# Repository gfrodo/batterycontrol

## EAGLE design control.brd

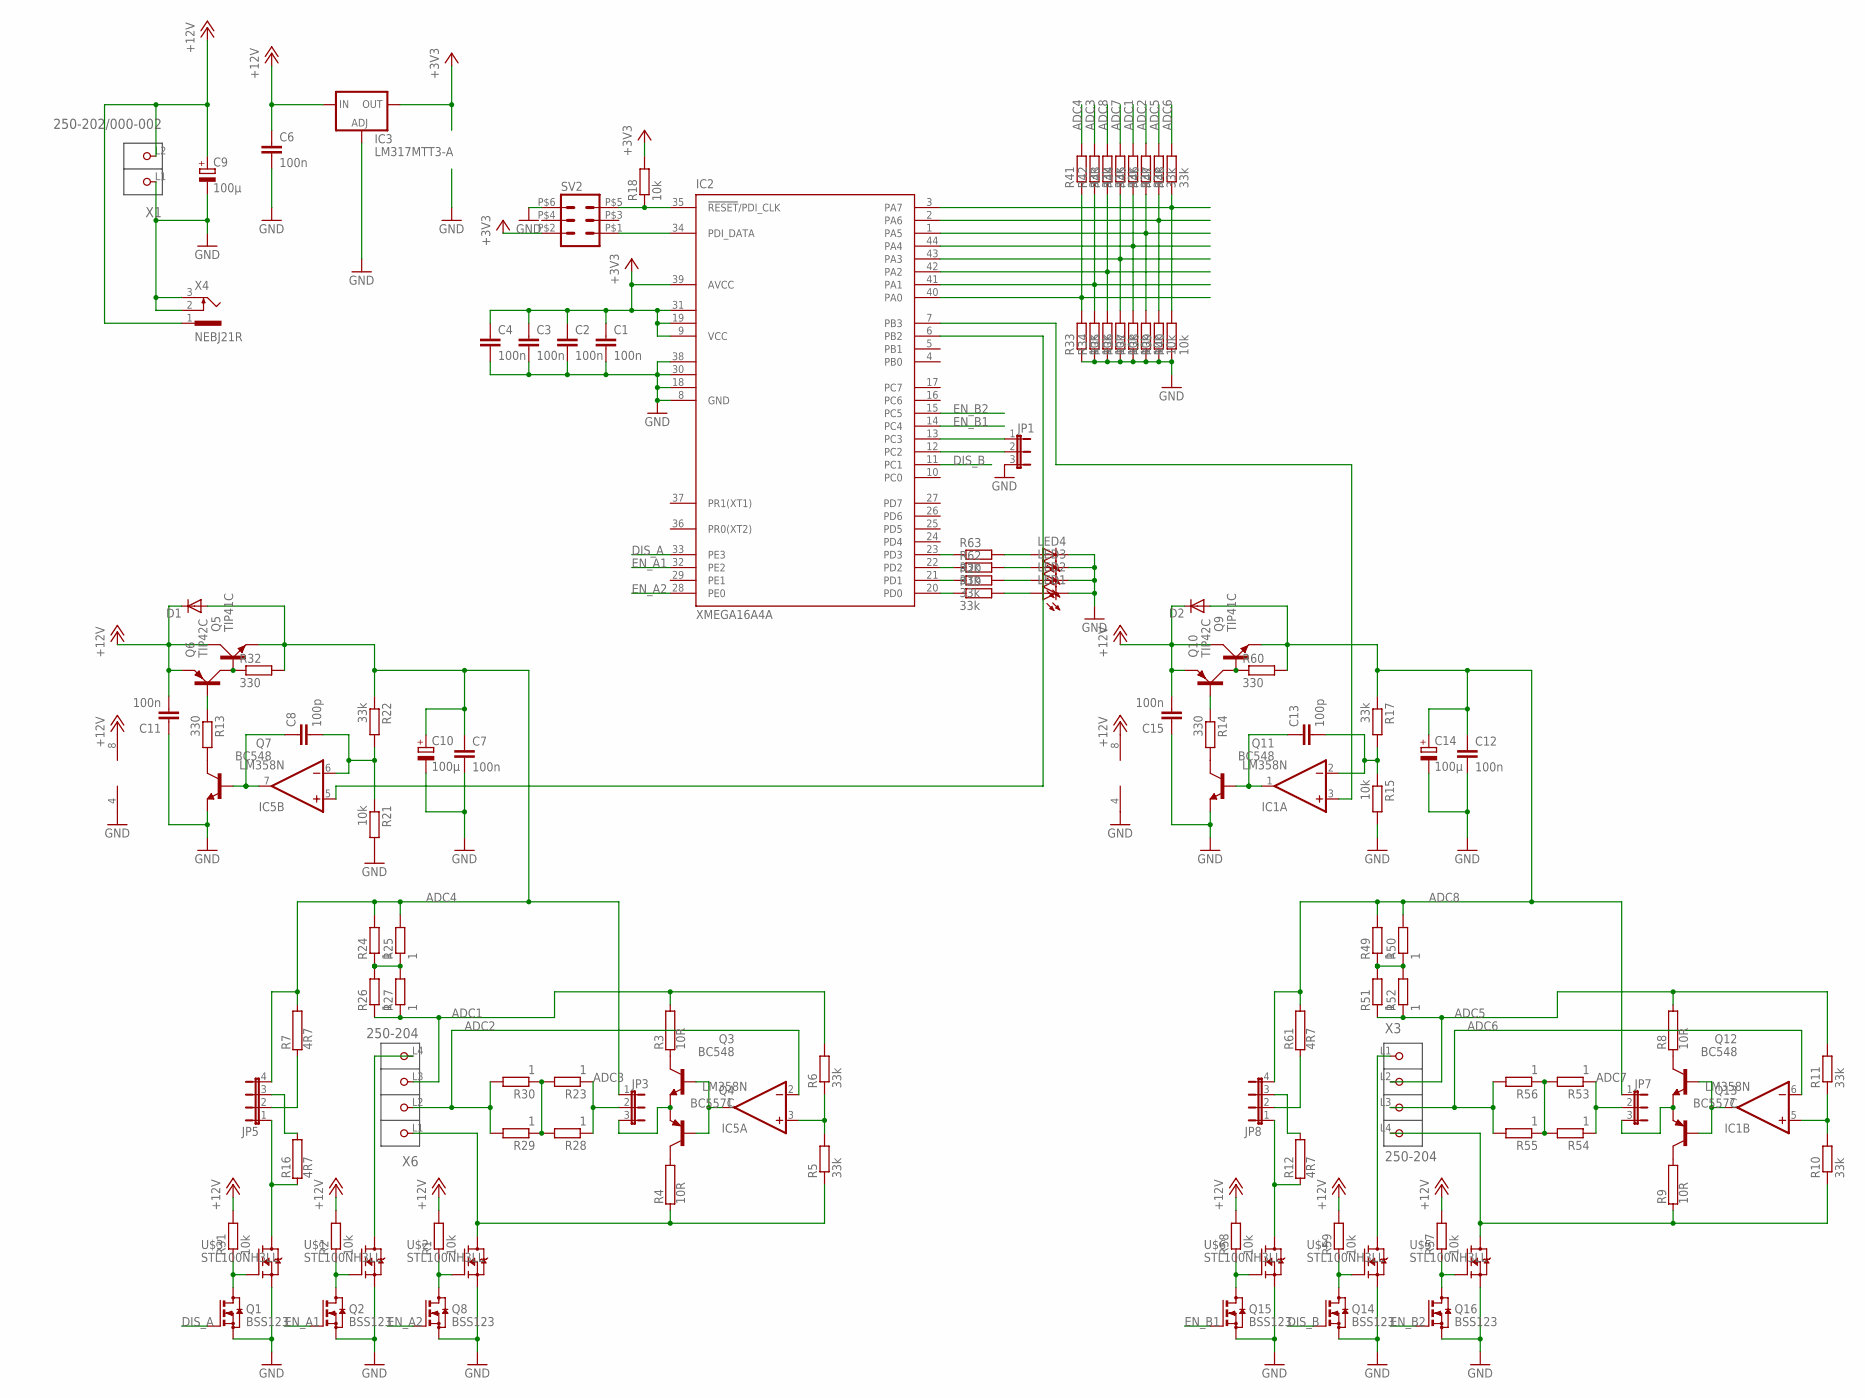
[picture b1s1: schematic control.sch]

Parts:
C1, C2, C3, C4, C6, C7, C12: 100n; C0805K
C8, C13: 100p; C0805K
C9, C10, C14: 100µ; E2,5-7
C11, C15: 100n; C0805
D1, D2: DIODE-DO41-7.6; DO41-7.6
IC1, IC5: LM358N; DIL08
IC2: XMEGA16A4A; TQFP44
IC3: LM317MTT3-A; SOT223
JP1, JP3, JP7: JP2E; JP2
JP5, JP8: JP4E; JP4
LED1, LED2, LED3, LED4: LEDCHIPLED_0805; CHIPLED_0805
Q1, Q2, Q8, Q14, Q15, Q16: BSS123; SOT23
Q3, Q7, Q11, Q12: BC548; TO92-EBC
Q4, Q13: BC557C; TO92-EBC
Q5, Q9: TIP41C; TO220AV
Q6, Q10: TIP42C; TO220AV
R1, R2, R15, R18, R21, R31, R33, R34, R35, R36, R37, R38, R39, R40, R57, R58, R59: 10k; M0805
R3, R4, R8, R9: 10R; HPS58
R5, R6, R10, R11, R17, R19, R20, R22, R41, R42, R43, R44, R45, R46, R47, R48, R62, R63: 33k; M0805
R7, R12, R16, R61: 4R7; KH208R-8
R13, R14, R32, R60: 330; M0805
R23, R24, R25, R26, R27, R28, R29, R30, R49, R50, R51, R52, R53, R54, R55, R56: 1; 0207/2V
SV2: ML66S; ML6S
U$1, U$2, U$3, U$4, U$5, U$6: STL100NH3LL; PG-TDSON-8
X1: 250-202/000-002; P-250-202
X3, X6: 250-204; P-250-204
X4: NEBJ21R

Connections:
+3V3: C1.1, C2.1, C3.1, C4.1, IC2.9 (VCC), IC2.19 (VCC1), IC2.31 (VCC2), IC2.39 (AVCC), IC3.2 (OUT), R18.2, SV2.P$2 (2)
+12V: C6.1, C9.+, C11.2, C15.2, D1.C, D2.C, IC1.8 (V+), IC3.3 (IN), IC5.8 (V+), Q5.C, Q6.E, Q9.C, Q10.E, R1.2, R2.2, R31.2, R57.2, R58.2, R59.2, X1.L2 (P2), X4.1
ADC1: R3.2, R6.2, R26.1, R27.1, R45.2, X6.L3 (P3)
ADC2: IC5.2 (-IN), R29.2, R30.2, R46.2, X6.L2 (P2)
ADC3: JP3.2, R23.1, R28.1, R42.2
ADC4: C7.1, C10.+, D1.A, JP3.1, JP5.4, Q5.E, R7.2, R22.1, R24.2, R25.2, R32.2, R41.2
ADC5: R8.2, R11.2, R47.2, R51.1, R52.1, X3.L2 (P2)
ADC6: IC1.6 (-IN), R48.2, R55.2, R56.2, X3.L3 (P3)
ADC7: JP7.2, R44.2, R53.1, R54.1
ADC8: C12.1, C14.+, D2.A, JP7.1, JP8.4, Q9.E, R17.1, R43.2, R49.2, R50.2, R60.2, R61.2
DIS_A: IC2.33 (PE3), Q1.1 (G)
DIS_B: IC2.11 (PC1), Q14.1 (G)
EN_A1: IC2.32 (PE2), Q2.1 (G)
EN_A2: IC2.28 (PE0), Q8.1 (G)
EN_B1: IC2.14 (PC4), Q15.1 (G)
EN_B2: IC2.15 (PC5), Q16.1 (G)
GND: C1.2, C2.2, C3.2, C4.2, C6.2, C7.2, C9.-, C10.-, C11.1, C12.2, C14.-, C15.1, IC1.4 (V-), IC2.8 (GND), IC2.18 (GND1), IC2.30 (GND2), IC2.38 (GND3), IC3.1 (ADJ), IC5.4 (V-), JP1.3, LED1.C, LED2.C, LED3.C, LED4.C, Q1.2 (S), Q2.2 (S), Q7.E, Q8.2 (S), Q11.E, Q14.2 (S), Q15.2 (S), Q16.2 (S), R15.2, R21.2, R33.1, R34.1, R35.1, R36.1, R37.1, R38.1, R39.1, R40.1, SV2.P$6 (6), U$1.1 (S), U$1.2 (S), U$1.3 (S), U$2.1 (S), U$2.2 (S), U$2.3 (S), U$3.1 (S), U$3.2 (S), U$3.3 (S), U$4.1 (S), U$4.2 (S), U$4.3 (S), U$5.1 (S), U$5.2 (S), U$5.3 (S), U$6.1 (S), U$6.2 (S), U$6.3 (S), X1.L1 (P1), X4.2, X4.3
unnamed: R4.1, R5.1, U$2.5 (D), U$2.6 (D), U$2.7 (D), U$2.8 (D), U$2.TH (D), X6.L1 (P1)
unnamed: R9.1, R10.1, U$5.5 (D), U$5.6 (D), U$5.7 (D), U$5.8 (D), U$5.TH (D), X3.L4 (P4)
unnamed: U$4.5 (D), U$4.6 (D), U$4.7 (D), U$4.8 (D), U$4.TH (D), X3.L1 (P1)
unnamed: U$1.5 (D), U$1.6 (D), U$1.7 (D), U$1.8 (D), U$1.TH (D), X6.L4 (P4)
unnamed: IC2.20 (PD0), R19.1
unnamed: Q1.3 (D), R31.1, U$3.4 (G)
unnamed: Q3.C, R3.1
unnamed: Q4.C, R4.2
unnamed: IC5.1 (OUT), Q3.B, Q4.B
unnamed: IC2.21 (PD1), R20.1
unnamed: IC5.3 (+IN), R5.2, R6.1
unnamed: Q12.C, R8.1
unnamed: Q7.C, R13.2
unnamed: JP5.1, R16.1, U$3.5 (D), U$3.6 (D), U$3.7 (D), U$3.8 (D), U$3.TH (D)
unnamed: JP5.3, R16.2
unnamed: JP5.2, R7.1
unnamed: IC2.35 (!RESET!/PDI_CLK), R18.1, SV2.P$5 (5)
unnamed: IC2.40 (PA0), R33.2, R41.1
unnamed: IC2.41 (PA1), R34.2, R42.1
unnamed: IC2.42 (PA2), R35.2, R43.1
unnamed: IC2.43 (PA3), R36.2, R44.1
unnamed: IC2.44 (PA4), R37.2, R45.1
unnamed: IC2.1 (PA5), R38.2, R46.1
unnamed: IC2.2 (PA6), R39.2, R47.1
unnamed: IC2.3 (PA7), R40.2, R48.1
unnamed: Q6.B, R13.1
unnamed: IC2.13 (PC3), JP1.1
unnamed: C8.1, IC5.7 (OUT), Q7.B
unnamed: R23.2, R28.2, R29.1, R30.1
unnamed: C8.2, IC5.6 (-IN), R21.1, R22.2
unnamed: IC2.6 (PB2), IC5.5 (+IN)
unnamed: Q5.B, Q6.C, R32.1
unnamed: R24.1, R25.1, R26.2, R27.2
unnamed: JP3.3, Q3.E, Q4.E
unnamed: Q2.3 (D), R2.1, U$1.4 (G)
unnamed: Q8.3 (D), R1.1, U$2.4 (G)
unnamed: Q13.C, R9.2
unnamed: IC2.12 (PC2), JP1.2
unnamed: IC2.22 (PD2), R62.1
unnamed: IC1.7 (OUT), Q12.B, Q13.B
unnamed: IC1.5 (+IN), R10.2, R11.1
unnamed: JP8.1, R12.1, U$6.5 (D), U$6.6 (D), U$6.7 (D), U$6.8 (D), U$6.TH (D)
unnamed: JP8.3, R12.2
unnamed: IC2.34 (PDI_DATA), SV2.P$1 (1)
unnamed: JP8.2, R61.1
unnamed: C13.1, IC1.1 (OUT), Q11.B
unnamed: C13.2, IC1.2 (-IN), R15.1, R17.2
unnamed: IC1.3 (+IN), IC2.7 (PB3)
unnamed: Q9.B, Q10.C, R60.1
unnamed: Q11.C, R14.2
unnamed: Q10.B, R14.1
unnamed: R49.1, R50.1, R51.2, R52.2
unnamed: R53.2, R54.2, R55.1, R56.1
unnamed: JP7.3, Q12.E, Q13.E
unnamed: Q14.3 (D), R59.1, U$4.4 (G)
unnamed: Q15.3 (D), R58.1, U$6.4 (G)
unnamed: Q16.3 (D), R57.1, U$5.4 (G)
unnamed: IC2.23 (PD3), R63.1
unnamed: LED4.A, R63.2
unnamed: LED3.A, R62.2
unnamed: LED2.A, R20.2
unnamed: LED1.A, R19.2

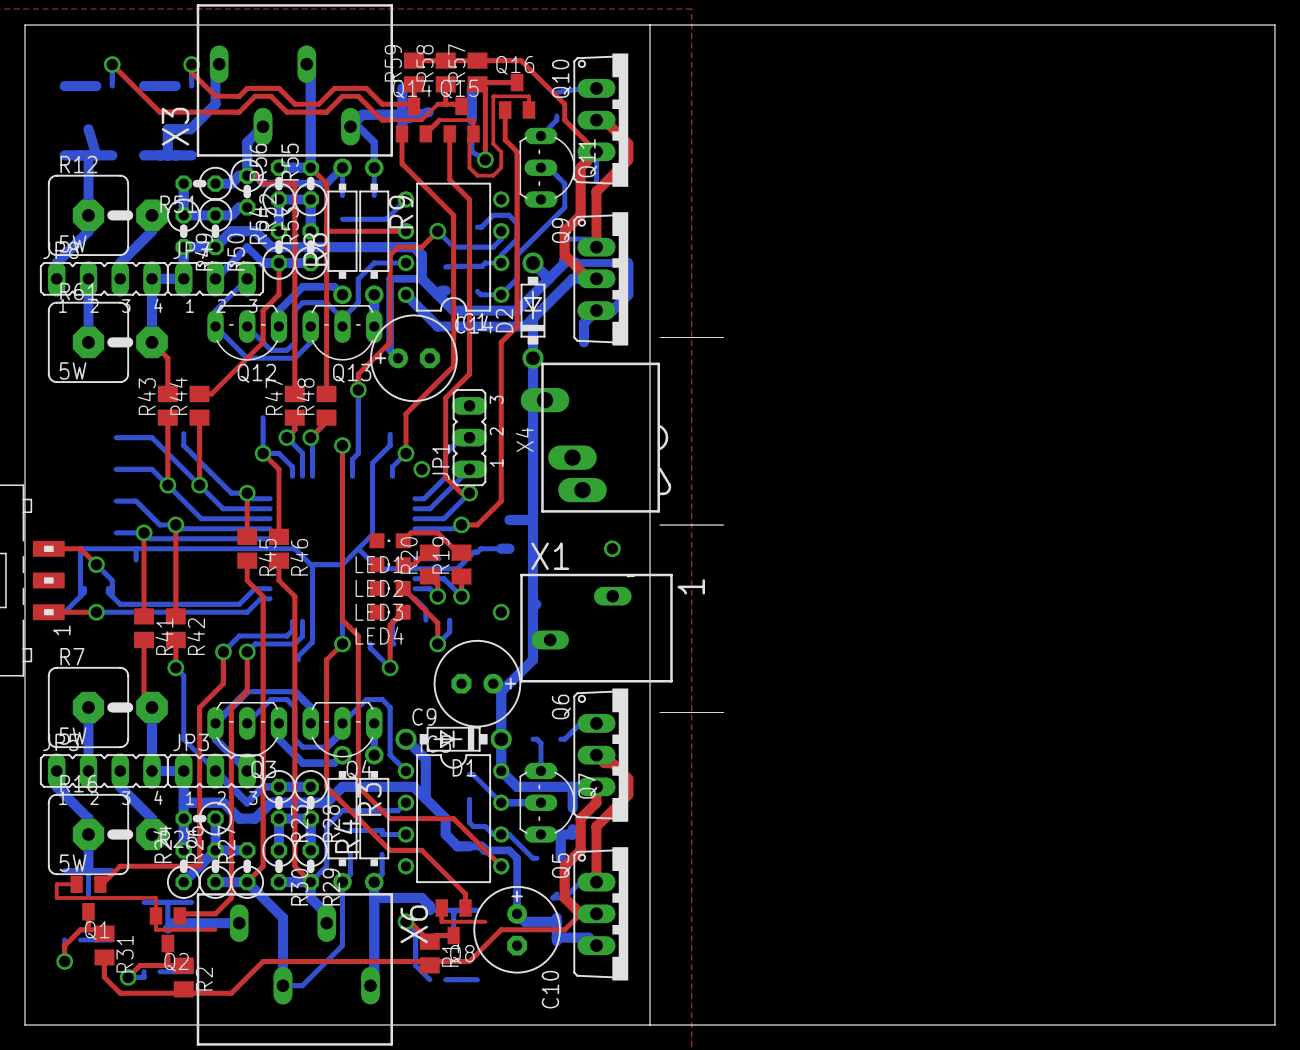
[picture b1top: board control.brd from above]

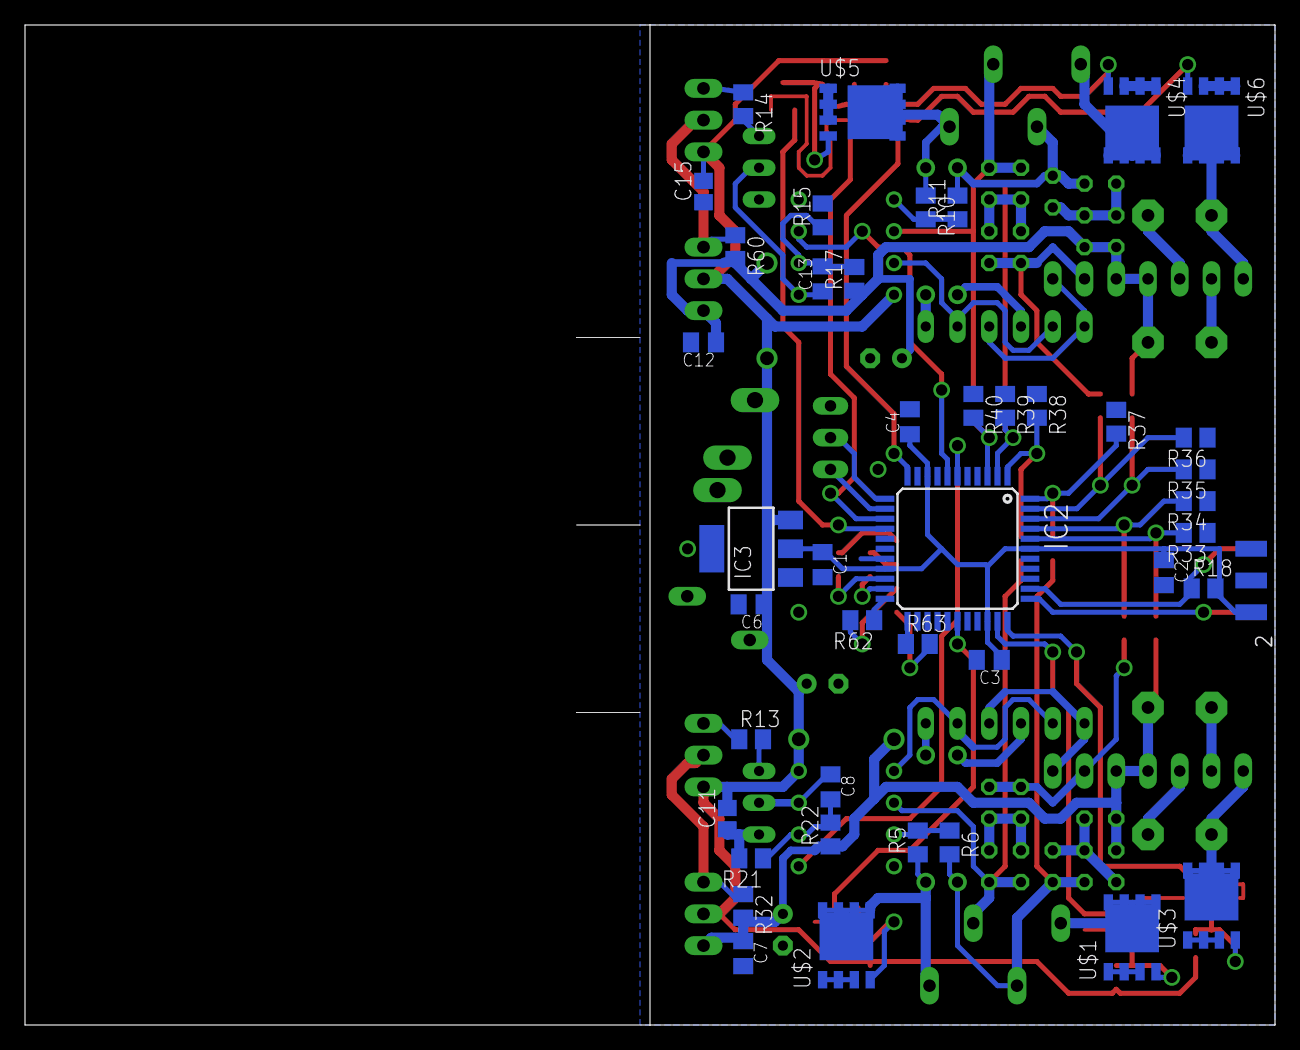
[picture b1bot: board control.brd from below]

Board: 2 copper layers, 100.0 x 80.0 mm, 119 parts (42 on the bottom side), 79 nets.

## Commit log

2017-05-11 initial
2017-05-11 +added main discharge path
2017-05-11 adc angeschlossen
2017-05-11 layer korrigiert
2017-05-11 routing
2017-05-11 DAC pin corrected
2017-05-11 duplicated balancer and voltager regulator
2017-05-11 noch falsche layer
2017-05-11 +spannungsregler
2017-05-11 small improvements
2017-05-11 shrinking
2017-05-11 routing, voltage dividers
2017-05-11 klemmen ersetzt
2017-05-11 GND polygon, schaltplan aufräumen
2017-05-11 opamp gateswap, fet driver move
2017-05-11 power connector hohlstecker
2017-05-11 LEDs
2017-05-11 transistor to bc548
2017-05-11 text added, isolate
2017-05-11 gnd vias
2017-05-11 author name added
